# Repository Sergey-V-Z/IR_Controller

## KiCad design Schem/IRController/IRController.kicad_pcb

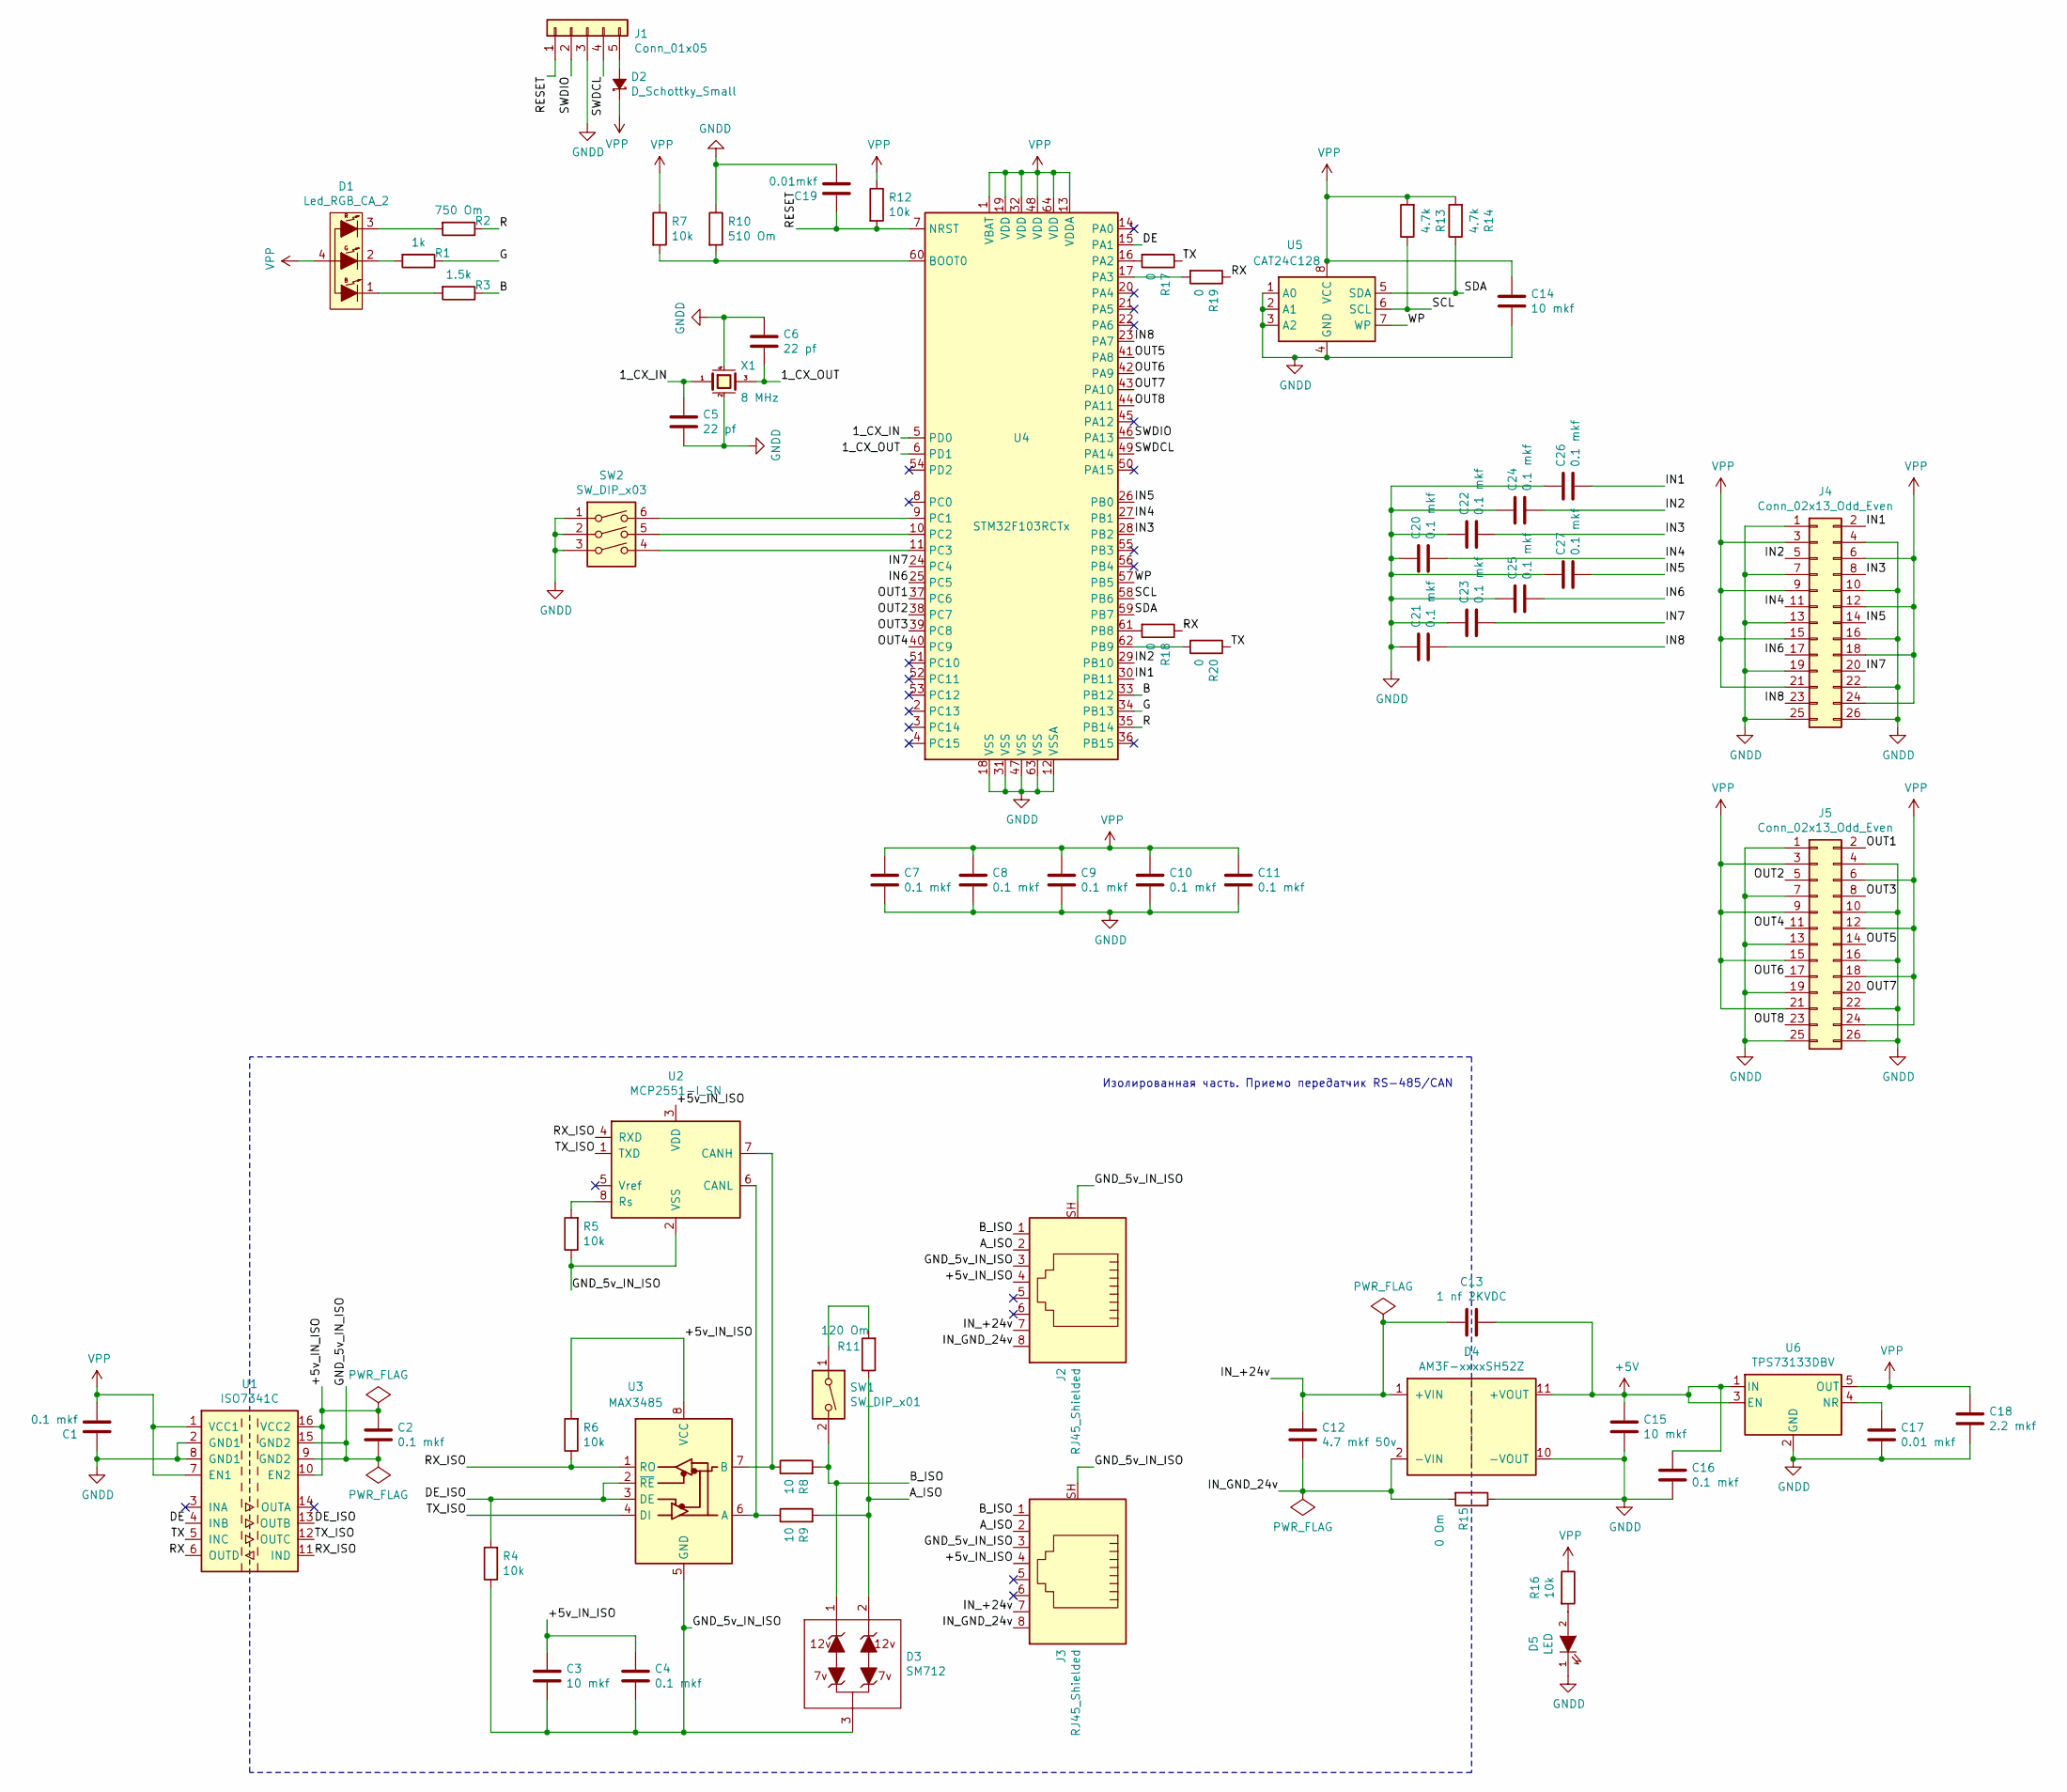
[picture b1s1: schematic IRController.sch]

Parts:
C1, C2, C4, C7, C8, C9, C10, C11, C20, C21, C22, C23, C24, C25, C26, C27: 0.1 mkf; C_0603_1608Metric_Pad1.05x0.95mm_HandSolder
C3, C14, C15: 10 mkf; C_0805_2012Metric_Pad1.15x1.40mm_HandSolder
C5, C6: 22 pf; C_0603_1608Metric_Pad1.05x0.95mm_HandSolder
C12: 4.7 mkf 50v; C_1206_3216Metric_Pad1.42x1.75mm_HandSolder
C13: 1 nf 2KVDC; C_Rect_L7.5mm_W6.5mm_P5.00mm
C16: 0.1 mkf; C_0805_2012Metric_Pad1.15x1.40mm_HandSolder
C17: 0.01 mkf; C_0805_2012Metric_Pad1.15x1.40mm_HandSolder
C18: 2.2 mkf; C_1206_3216Metric
C19: 0.01mkf; C_0603_1608Metric_Pad1.05x0.95mm_HandSolder
D1: Led_RGB_CA_2; LED_Avago_PLCC4_3.2x2.8mm_CW
D2: D_Schottky_Small; D_SMA-SMB_Universal_Handsoldering
D3: SM712; SOT-23
D4: AM3F-xxxxSH52Z; Converter_DCDC_AM3F-xxxxSH52Z_THT
D5: LED; LED_0805_2012Metric
J1: Conn_01x05; PinHeader_1x05_P2.54mm_Vertical
J2, J3: RJ45_Shielded; RJ45_Ninigi_GE
J4, J5: Conn_02x13_Odd_Even; IDC-Header_2x13_P2.54mm_Vertical
R1: 1k; R_0805_2012Metric_Pad1.15x1.40mm_HandSolder
R2: 750 Om; R_0805_2012Metric_Pad1.15x1.40mm_HandSolder
R3: 1.5k; R_0805_2012Metric_Pad1.15x1.40mm_HandSolder
R4, R5, R6, R7, R12, R16: 10k; R_0805_2012Metric_Pad1.15x1.40mm_HandSolder
R8, R9: 10; R_0805_2012Metric_Pad1.15x1.40mm_HandSolder
R10: 510 Om; R_0805_2012Metric_Pad1.15x1.40mm_HandSolder
R11: 120 Om; R_0805_2012Metric_Pad1.15x1.40mm_HandSolder
R13, R14: 4.7k; R_0805_2012Metric_Pad1.15x1.40mm_HandSolder
R15: 0 Om; R_1206_3216Metric_Pad1.42x1.75mm_HandSolder
R17, R18, R19, R20: 0; R_0805_2012Metric_Pad1.15x1.40mm_HandSolder
SW1: SW_DIP_x01; SW_DIP_SPSTx01_Slide_9.78x4.72mm_W7.62mm_P2.54mm
SW2: SW_DIP_x03; SW_DIP_SPSTx03_Slide_9.78x9.8mm_W7.62mm_P2.54mm
U1: ISO7341C; SOIC-16W_7.5x10.3mm_P1.27mm
U2: MCP2551-I_SN; SO-8_3.9x4.9mm_P1.27mm
U3: MAX3485; SOIC-8_3.9x4.9mm_P1.27mm
U4: STM32F103RCTx; LQFP-64_10x10mm_P0.5mm
U5: CAT24C128; SOIC-8_3.9x4.9mm_P1.27mm
U6: TPS73133DBV; SOT-23-5
X1: 8 MHz; Crystal_SMD_5032-4Pin_5.0x3.2mm

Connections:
+5V: C13.1, C15.1, C16.1, D4.11 (+VOUT), U6.1 (IN), U6.3 (EN)
/1_CX_IN: C5.1, U4.5 (PD0), X1.1
/1_CX_OUT: C6.2, U4.6 (PD1), X1.3
/+5v_IN_ISO: C2.1, C3.1, C4.1, J2.4, J3.4, R6.2, U1.10 (EN2), U1.16 (VCC2), U2.3 (VDD), U3.8 (VCC)
/A_ISO: D3.2, J2.2, J3.2, R9.2, R11.1
/B: R3.1, U4.33 (PB12)
/B_ISO: D3.1, J2.1, J3.1, R8.2, SW1.2
/DE: U1.4 (INB), U4.15 (PA1)
/DE_ISO: R4.2, U1.13 (OUTB), U3.2 (~RE), U3.3 (DE)
/G: R1.1, U4.34 (PB13)
/GND_5v_IN_ISO: C2.2, C3.2, C4.2, D3.3, J2.3, J2.SH, J3.3, J3.SH, R4.1, R5.1, U1.9 (GND2), U1.15 (GND2), U2.2 (VSS), U3.5 (GND)
/IN1: C26.2, J4.2, U4.30 (PB11)
/IN2: C24.2, J4.5, U4.29 (PB10)
/IN3: C22.2, J4.8, U4.28 (PB2)
/IN4: C20.2, J4.11, U4.27 (PB1)
/IN5: C27.2, J4.14, U4.26 (PB0)
/IN6: C25.2, J4.17, U4.25 (PC5)
/IN7: C23.2, J4.20, U4.24 (PC4)
/IN8: C21.2, J4.23, U4.23 (PA7)
/IN_+24v: C12.1, C13.2, D4.1 (+VIN), J2.7, J3.7
/IN_GND_24v: C12.2, D4.2 (-VIN), J2.8, J3.8, R15.2
/OUT1: J5.2, U4.37 (PC6)
/OUT2: J5.5, U4.38 (PC7)
/OUT3: J5.8, U4.39 (PC8)
/OUT4: J5.11, U4.40 (PC9)
/OUT5: J5.14, U4.41 (PA8)
/OUT6: J5.17, U4.42 (PA9)
/OUT7: J5.20, U4.43 (PA10)
/OUT8: J5.23, U4.44 (PA11)
/R: R2.1, U4.35 (PB14)
/RESET: C19.1, J1.1, R12.2, U4.7 (NRST)
/RX: R18.1, R19.1, U1.6 (OUTD)
/RX_ISO: R6.1, U1.11 (IND), U2.4 (RXD), U3.1 (RO)
/SCL: R13.1, U4.58 (PB6), U5.6 (SCL)
/SDA: R14.1, U4.59 (PB7), U5.5 (SDA)
/SWDCL: J1.4, U4.49 (PA14)
/SWDIO: J1.2, U4.46 (PA13)
/TX: R17.1, R20.1, U1.5 (INC)
/TX_ISO: U1.12 (OUTC), U2.1 (TXD), U3.4 (DI)
/WP: U4.57 (PB5), U5.7 (WP)
GNDD: C1.1, C5.2, C6.1, C7.2, C8.2, C9.2, C10.2, C11.2, C14.2, C15.2, C16.2, C17.2, C18.2, C19.2, C20.1, C21.1, C22.1, C23.1, C24.1, C25.1, C26.1, C27.1, D4.10 (-VOUT), D5.1 (K), J1.3, J4.1, J4.4, J4.7, J4.10, J4.13, J4.16, J4.19, J4.22, J4.25, J4.26, J5.1, J5.4, J5.7, J5.10, J5.13, J5.16, J5.19, J5.22, J5.25, J5.26, R10.1, R15.1, SW2.1, SW2.2, SW2.3, U1.2 (GND1), U1.8 (GND1), U4.12 (VSSA), U4.18 (VSS), U4.31 (VSS), U4.47 (VSS), U4.63 (VSS), U5.1 (A0), U5.2 (A1), U5.3 (A2), U5.4 (GND), U6.2 (GND), X1.2 (case), X1.4 (case)
unnamed: C17.1, U6.4 (NR)
unnamed: D1.1 (B), R3.2
unnamed: D1.2 (G), R1.2
unnamed: D1.3 (R), R2.2
unnamed: D2.2 (A), J1.5
unnamed: D5.2 (A), R16.2
unnamed: R5.2, U2.8 (Rs)
unnamed: R8.1, U2.7 (CANH), U3.7 (B)
unnamed: R9.1, U2.6 (CANL), U3.6 (A)
unnamed: R7.2, R10.2, U4.60 (BOOT0)
unnamed: R11.2, SW1.1
unnamed: R17.2, U4.16 (PA2)
unnamed: R18.2, U4.61 (PB8)
unnamed: R19.2, U4.17 (PA3)
unnamed: R20.2, U4.62 (PB9)
unnamed: SW2.4, U4.11 (PC3)
unnamed: SW2.5, U4.10 (PC2)
unnamed: SW2.6, U4.9 (PC1)
VPP: C1.2, C7.1, C8.1, C9.1, C10.1, C11.1, C14.1, C18.1, D1.4, D2.1 (K), J4.3, J4.6, J4.9, J4.12, J4.15, J4.18, J4.21, J4.24, J5.3, J5.6, J5.9, J5.12, J5.15, J5.18, J5.21, J5.24, R7.1, R12.1, R13.2, R14.2, R16.1, U1.1 (VCC1), U1.7 (EN1), U4.1 (VBAT), U4.13 (VDDA), U4.19 (VDD), U4.32 (VDD), U4.48 (VDD), U4.64 (VDD), U5.8 (VCC), U6.5 (OUT)

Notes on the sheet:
Изолированная часть. Приемо передатчик RS-485/CAN

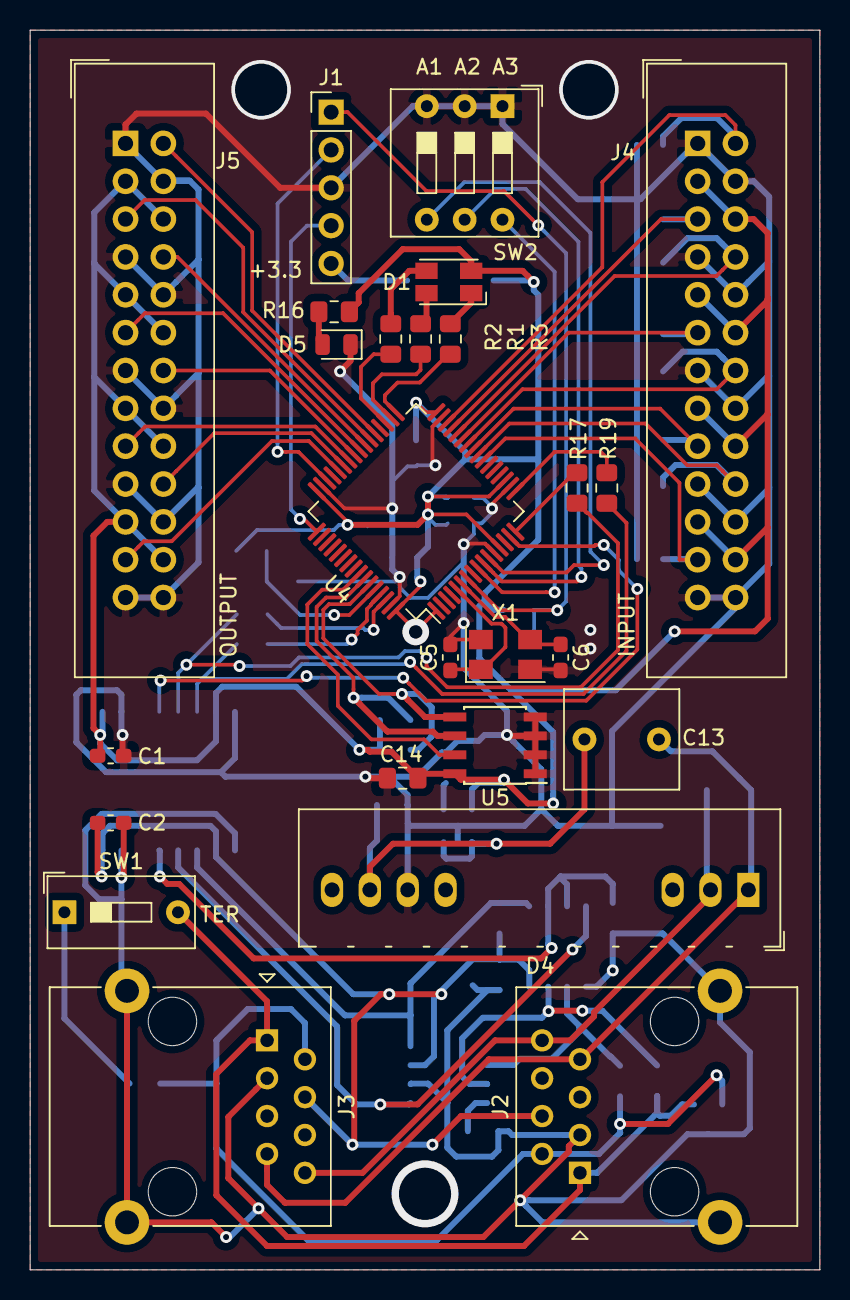
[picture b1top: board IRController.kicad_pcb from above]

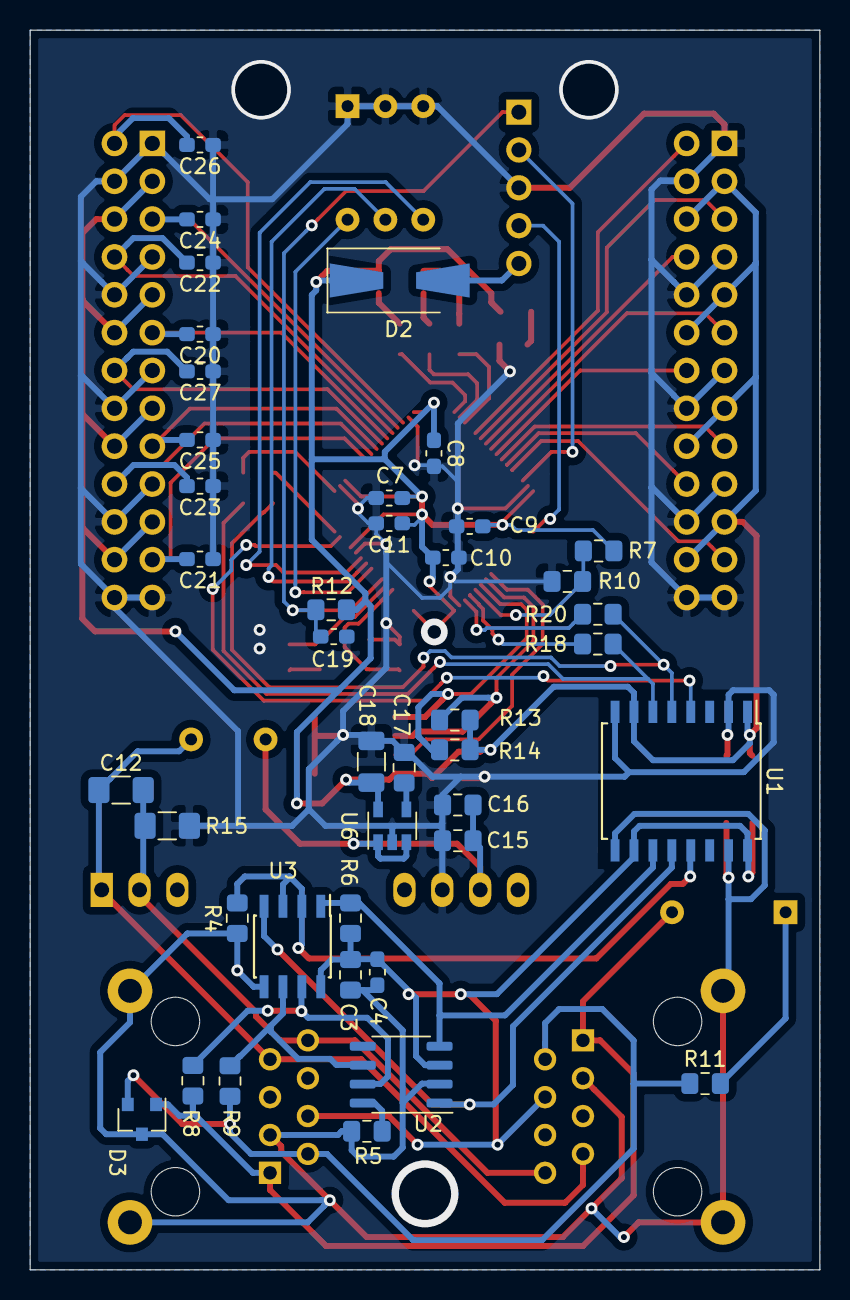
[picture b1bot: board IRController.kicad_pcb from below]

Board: 2 copper layers, 53.0 x 83.2 mm, 66 parts (41 on the bottom side), 60 nets.

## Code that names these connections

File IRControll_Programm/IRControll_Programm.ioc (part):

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Mcu.Name=STM32F103R(C-D-E)Tx
Mcu.Package=LQFP64
Mcu.UserName=STM32F103RCTx
PA1.GPIOParameters=GPIO_Label
PA1.GPIO_Label=DE
PA1.Signal=GPIO_Output
PA10.GPIOParameters=GPIO_Label
PA10.GPIO_Label=OUT7
PA10.Signal=S_TIM1_CH3
PA11.GPIOParameters=GPIO_Label
PA11.GPIO_Label=OUT8
PA11.Signal=S_TIM1_CH4
PA13.Mode=Serial_Wire
PA13.Signal=SYS_JTMS-SWDIO
PA14.Mode=Serial_Wire
PA14.Signal=SYS_JTCK-SWCLK
PA2.Mode=Asynchronous
PA2.Signal=USART2_TX
PA3.Mode=Asynchronous
PA3.Signal=USART2_RX
PA7.GPIOParameters=GPIO_PuPd,GPIO_Label
PA7.GPIO_Label=IN8
PA7.GPIO_PuPd=GPIO_PULLUP
PA7.Signal=GPIO_Input
PA8.GPIOParameters=GPIO_Label
PA8.GPIO_Label=OUT5
PA8.Signal=S_TIM1_CH1
PA9.GPIOParameters=GPIO_Label
PA9.GPIO_Label=OUT6
PA9.Signal=S_TIM1_CH2
PB0.GPIOParameters=GPIO_PuPd,GPIO_Label
PB0.GPIO_Label=IN5
PB0.GPIO_PuPd=GPIO_PULLUP
PB0.Signal=GPIO_Input
PB1.GPIOParameters=GPIO_PuPd,GPIO_Label
PB1.GPIO_Label=IN4
PB1.GPIO_PuPd=GPIO_PULLUP
PB1.Signal=GPIO_Input
PB10.GPIOParameters=GPIO_PuPd,GPIO_Label
PB10.GPIO_Label=IN2
PB10.GPIO_PuPd=GPIO_PULLUP
PB10.Signal=GPIO_Input
PB11.GPIOParameters=GPIO_PuPd,GPIO_Label
PB11.GPIO_Label=IN1
PB11.GPIO_PuPd=GPIO_PULLUP
PB11.Signal=GPIO_Input
PB12.GPIOParameters=GPIO_Label
PB12.GPIO_Label=B
PB12.Signal=GPIO_Output
PB13.GPIOParameters=GPIO_Label
PB13.GPIO_Label=G
PB13.Signal=GPIO_Output
PB14.GPIOParameters=GPIO_Label
PB14.GPIO_Label=R
PB14.Signal=GPIO_Output
PB2.GPIOParameters=GPIO_PuPd,GPIO_Label
PB2.GPIO_Label=IN3
PB2.GPIO_PuPd=GPIO_PULLUP
PB2.Signal=GPIO_Input
PB6.Mode=I2C
PB6.Signal=I2C1_SCL
PB7.Mode=I2C
PB7.Signal=I2C1_SDA
PC1.GPIOParameters=GPIO_PuPd
PC1.GPIO_PuPd=GPIO_PULLUP
PC1.Signal=GPIO_Input
PC2.GPIOParameters=GPIO_PuPd
PC2.GPIO_PuPd=GPIO_PULLUP
PC2.Signal=GPIO_Input
PC3.GPIOParameters=GPIO_PuPd
PC3.GPIO_PuPd=GPIO_PULLUP
PC3.Signal=GPIO_Input
PC4.GPIOParameters=GPIO_PuPd,GPIO_Label
PC4.GPIO_Label=IN7
PC4.GPIO_PuPd=GPIO_PULLUP
PC4.Signal=GPIO_Input
PC5.GPIOParameters=GPIO_PuPd,GPIO_Label
PC5.GPIO_Label=IN6
PC5.GPIO_PuPd=GPIO_PULLUP
PC5.Signal=GPIO_Input
PC6.GPIOParameters=GPIO_Label
PC6.GPIO_Label=OUT1
PC6.Signal=S_TIM8_CH1
PC7.GPIOParameters=GPIO_Label
PC7.GPIO_Label=OUT2
PC7.Signal=S_TIM8_CH2
PC8.GPIOParameters=GPIO_Label
PC8.GPIO_Label=OUT3
PC8.Signal=S_TIM8_CH3
PC9.GPIOParameters=GPIO_Label
PC9.GPIO_Label=OUT4
PC9.Signal=S_TIM8_CH4
PD0-OSC_IN.Mode=HSE-External-Oscillator
PD0-OSC_IN.Signal=RCC_OSC_IN
PD1-OSC_OUT.Mode=HSE-External-Oscillator
PD1-OSC_OUT.Signal=RCC_OSC_OUT
RCC.HSE_VALUE=12000000
RCC.SYSCLKFreq_VALUE=72000000
RCC.SYSCLKSource=RCC_SYSCLKSOURCE_PLLCLK
board=custom

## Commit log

2020-07-14 Первый
2021-03-02 next
2021-03-02 Sensors add
2021-03-03 add class
2021-03-04 First test
2021-03-10 F303 probe
2021-03-10 f303
    Переписал на f303 исправил ошибки
